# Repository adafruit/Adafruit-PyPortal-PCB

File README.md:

## Adafruit PyPortal - CircuitPython Powered Internet Display PCB

<br/>
<br/>
<br/>

PCB files for the Adafruit PyPortal - CircuitPython Powered Internet Display and PyPortal Pynt. Format is EagleCAD schematic and board layout
* https://www.adafruit.com/product/4116
* https://www.adafruit.com/product/4465
* https://www.adafruit.com/product/4444

### Description

**PyPortal**, our easy-to-use IoT device that allows you to create all the things for the “Internet of Things” in minutes. Make custom touch screen interface GUIs, all open-source, and Python-powered using tinyJSON / APIs to get news, stock, weather, cat photos, and more – all over Wi-Fi with the latest technologies. Create little pocket universes of joy that connect to something good. Rotate it 90 degrees, it’s a web-connected conference badge #badgelife.

The PyPortal uses an ATMEL (Microchip) ATSAMD51J20, and an Espressif ESP32 Wi-Fi coprocessor with TLS/SSL support built-in. PyPortal has a **3.2″ 320 x 240 color TFT** with resistive touch screen. PyPortal includes: speaker, light sensor, temperature sensor, NeoPixel, microSD card slot, 8MB flash, plug-in ports for I2C and 2 analog/digital pins, 3D files for custom enclosures / lanyard fastening. Open-source hardware, and Open-Source software, CircuitPython and Arduino. The device shows up as a USB drive and the code (Python) can be edited in any IDE, text editor, etc.

The PyPortal Pynt is the little sister to our popular PyPortal - zapped with a shink ray to take the design from a 3.2" diagonal down to 2.4" diagonal screen - but otherwise the same! **Compared to the PyPortal, the Pynt does not include a ADT7410 temperature sensor. Other than the ADT7410, the Pynt's display, processor, STEMMA conectors and WiFi have the exact same wiring as the original 3.2" PyPortal so all Arduino/CircuitPython code will run exactly the same - just smaller!**

The M4 and ESP32 are a great couple - and each bring their own strengths to this board. The SAMD51 M4 has native USB so it can show up like a disk drive, act as a MIDI or HID keyboard/mouse, and of course bootload and debug over a serial port. It also has DACs, ADC, PWM, and tons of GPIO. Meanwhile, the ESP32 has secure WiFi capabilities, and plenty of Flash and RAM to buffer sockets. By letting the ESP32 focus on the complex TLS/SSL computation and socket buffering, it frees up the SAMD51 to act as the user interface. You get a great programming experience thanks to the native USB with files available for drag-n-drop, and you don't have to spend a ton of processor time and memory to do SSL encryption/decryption and certificate management. It's the best of both worlds!

**Please note:** You may get a version with DigiKey + Analog Devices branding or in plain style. The hardware is identical.

### License

Adafruit invests time and resources providing this open source design, please support Adafruit and open-source hardware by purchasing products from [Adafruit](https://www.adafruit.com)!

Designed by Limor Fried/Ladyada for Adafruit Industries.

Creative Commons Attribution/Share-Alike, all text above must be included in any redistribution. See license.txt for additional details.

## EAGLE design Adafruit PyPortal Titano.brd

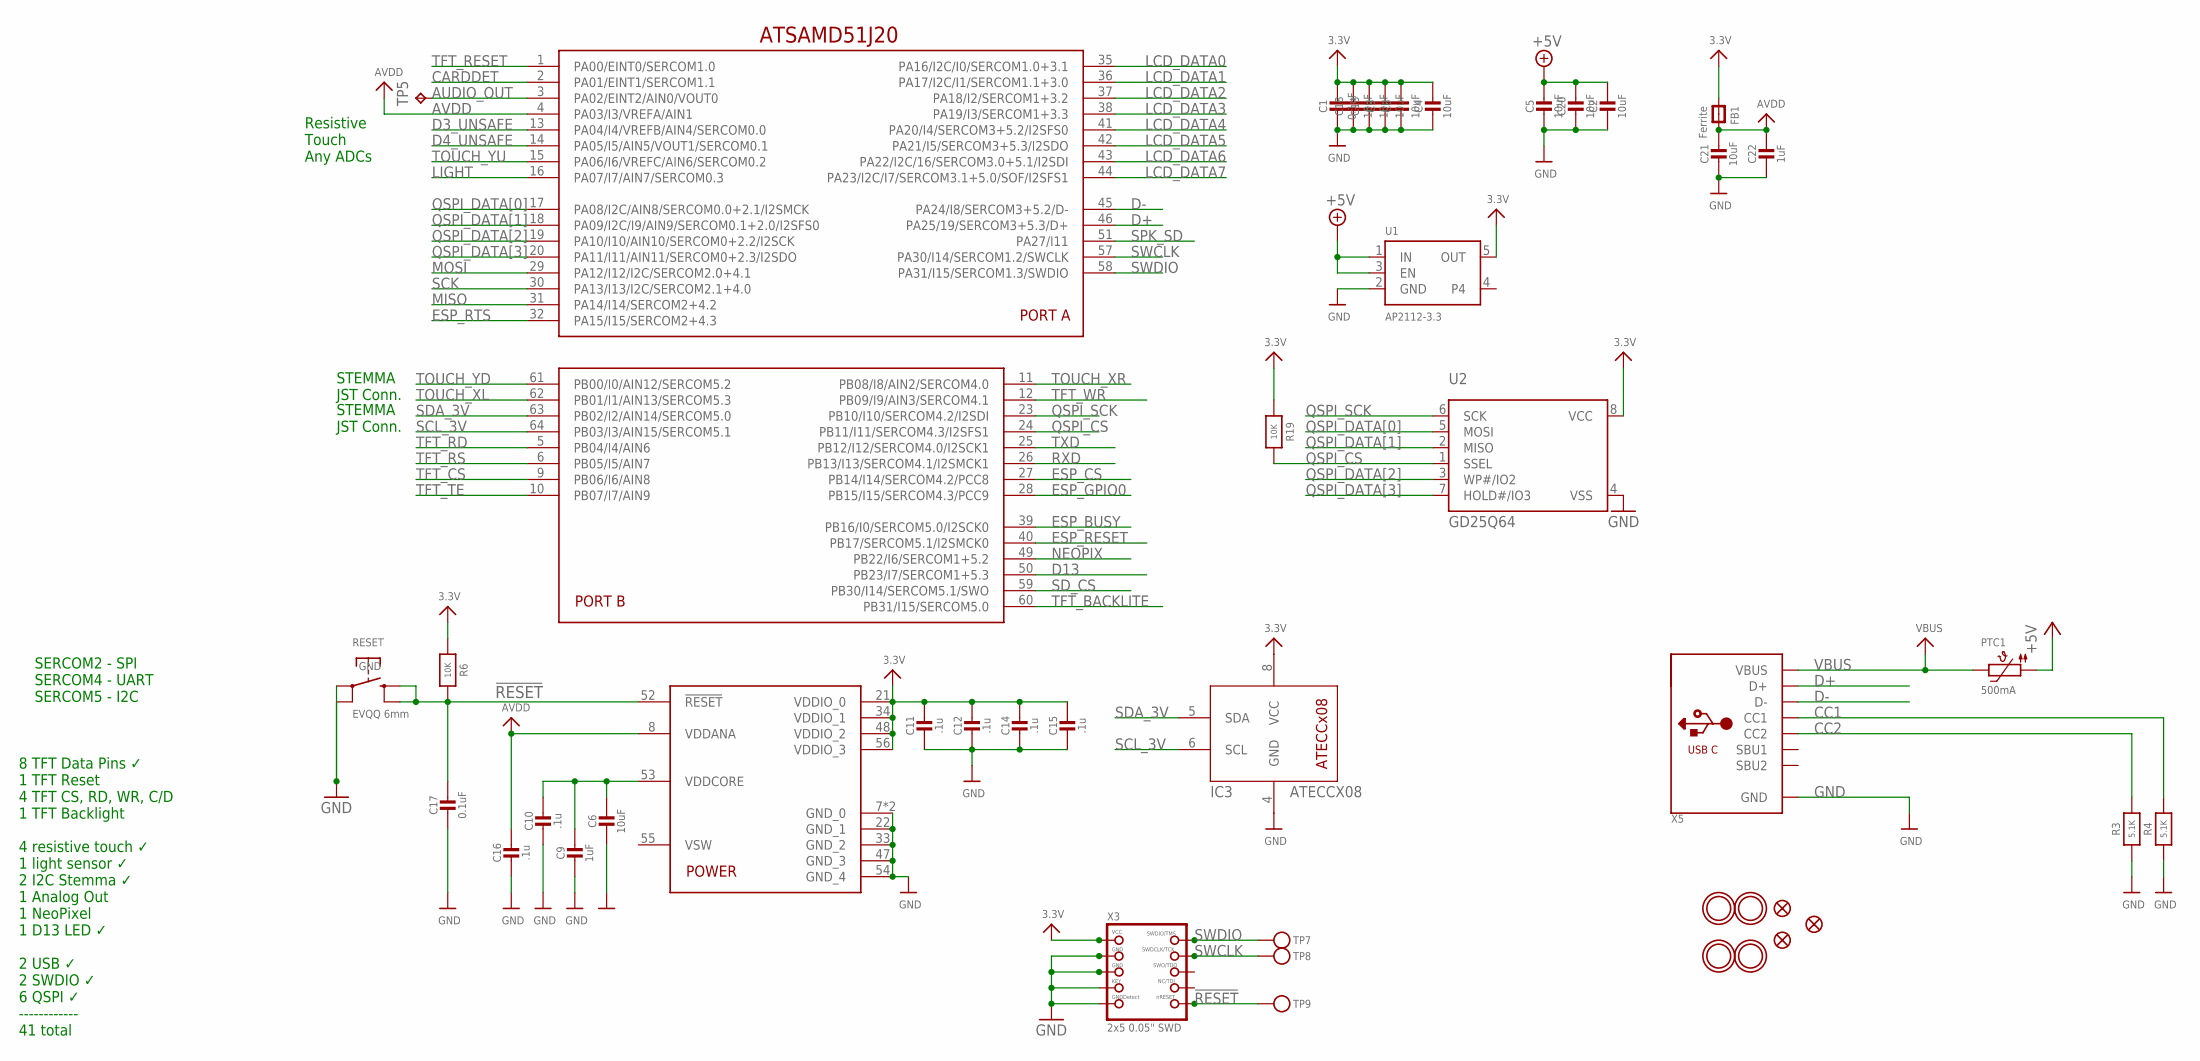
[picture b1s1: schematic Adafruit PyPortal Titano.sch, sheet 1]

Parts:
C1, C17: 0.1uF; 0603-NO
C2, C3, C4, C5, C6, C8, C13, C18, C20, C21: 10uF; 0805-NO
C9, C22: 1uF; 0603-NO
C10, C11, C12, C14, C15, C16: .1u; 0603-NO
FB1: Ferrite; 0805-NO
IC3: ATECCX08; SOIC8_150MIL
PTC1: 500mA; 1206
R3, R4: 5.1K; 0603-NO
R6, R19: 10K; 0603-NO
RESET: EVQQ 6mm; EVQ-Q2_SMALLER
TP5: TPTP15R; TP15R
TP7, TP8, TP9: TESTPOINTROUND1.5MM; TESTPOINT_ROUND_1.5MM
U1: AP2112-3.3; SOT23-5
U2: GD25Q64; SOIC8_208MIL
U$2: ATSAMD51J20; PQFN64-1
U$7, U$15, U$16, U$17: MOUNTINGHOLE3.0THIN; MOUNTINGHOLE_3.0_PLATEDTHIN
U$9, U$11, U$23: FIDUCIAL_1MM
X3: 2x5 0.05" SWD; 2X05_1.27MM_BOX_POSTS
X5: USB_C; USB_C_CUSB31-CFM2AX-01-X

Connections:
3.3V: C1.1, C3.1, C4.1, C8.1, C11.2, C12.2, C13.1, C14.2, C15.2, C18.1, FB1.1, IC3.8 (VCC), R6.1, R19.1, U1.5 (OUT), U2.8 (VCC), U$2.21 (VDDIO_0), U$2.34 (VDDIO_1), U$2.48 (VDDIO_2), U$2.56 (VDDIO_3), X3.1 (VCC); also elsewhere on the board
!RESET: C17.2, R6.2, RESET.B (S), RESET.B' (S1), TP9.P$1, U$2.52 (!RESET), X3.10 (NRESET)
+5V: C2.1, C5.1, C20.1, PTC1.1, U1.1 (IN), U1.3 (EN); also elsewhere on the board
AUDIO_OUT: TP5.TP, U$2.3 (PA02/EINT2/AIN0/VOUT0); also elsewhere on the board
AVDD: C16.2, C21.1, C22.1, FB1.2, U$2.4 (PA03/I3/VREFA/AIN1), U$2.8 (VDDANA)
CARDDET: U$2.2 (PA01/EINT1/SERCOM1.1); also elsewhere on the board
CC1: R4.2, X5.A5 (CC1)
CC2: R3.2, X5.B5 (CC2)
D3_UNSAFE: U$2.13 (PA04/I4/VREFB/AIN4/SERCOM0.0); also elsewhere on the board
D4_UNSAFE: U$2.14 (PA05/I5/AIN5/VOUT1/SERCOM0.1); also elsewhere on the board
D13: U$2.50 (PB23/I7/SERCOM1+5.3); also elsewhere on the board
D+: U$2.46 (PA25/19/SERCOM3+5.3/D+), X5.A6 (D+), X5.B6 (D+)
D-: U$2.45 (PA24/I8/SERCOM3+5.2/D-), X5.A7 (D-), X5.B7 (D-)
ESP_BUSY: U$2.39 (PB16/I0/SERCOM5.0/I2SCK0); also elsewhere on the board
ESP_CS: U$2.27 (PB14/I14/SERCOM4.2/PCC8); also elsewhere on the board
ESP_GPIO0: U$2.28 (PB15/I15/SERCOM4.3/PCC9); also elsewhere on the board
ESP_RESET: U$2.40 (PB17/SERCOM5.1/I2SMCK0); also elsewhere on the board
ESP_RTS: U$2.32 (PA15/I15/SERCOM2+4.3); also elsewhere on the board
GND: C1.2, C2.2, C3.2, C4.2, C5.2, C6.2, C8.2, C9.2, C10.1, C11.1, C12.1, C13.2, C14.1, C15.1, C16.1, C17.1, C18.2, C20.2, C21.2, C22.2, IC3.4 (GND), R3.1, R4.1, RESET.A, RESET.A' (P1), U1.2 (GND), U2.4 (VSS), U$2.7 (GND_0), U$2.22 (GND_1), U$2.33 (GND_2), U$2.47 (GND_3), U$2.54 (GND_4), U$2.EXP (GND_0), X3.3 (GND), X3.5 (GND), X3.7 (KEY), X3.9 (GNDDETECT), X5.A1B12 (GND), X5.B1A12 (GND); also elsewhere on the board
LCD_DATA0: U$2.35 (PA16/I2C/I0/SERCOM1.0+3.1); also elsewhere on the board
LCD_DATA1: U$2.36 (PA17/I2C/I1/SERCOM1.1+3.0); also elsewhere on the board
LCD_DATA2: U$2.37 (PA18/I2/SERCOM1+3.2); also elsewhere on the board
LCD_DATA3: U$2.38 (PA19/I3/SERCOM1+3.3); also elsewhere on the board
LCD_DATA4: U$2.41 (PA20/I4/SERCOM3+5.2/I2SFS0); also elsewhere on the board
LCD_DATA5: U$2.42 (PA21/I5/SERCOM3+5.3/I2SDO); also elsewhere on the board
LCD_DATA6: U$2.43 (PA22/I2C/16/SERCOM3.0+5.1/I2SDI); also elsewhere on the board
LCD_DATA7: U$2.44 (PA23/I2C/I7/SERCOM3.1+5.0/SOF/I2SFS1); also elsewhere on the board
LIGHT: U$2.16 (PA07/I7/AIN7/SERCOM0.3); also elsewhere on the board
MISO: U$2.31 (PA14/I14/SERCOM2+4.2); also elsewhere on the board
MOSI: U$2.29 (PA12/I12/I2C/SERCOM2.0+4.1); also elsewhere on the board
NEOPIX: U$2.49 (PB22/I6/SERCOM1+5.2); also elsewhere on the board
QSPI_CS: R19.2, U2.1 (SSEL), U$2.24 (PB11/I11/SERCOM4.3/I2SFS1)
QSPI_DATA[0]: U2.5 (MOSI), U$2.17 (PA08/I2C/AIN8/SERCOM0.0+2.1/I2SMCK)
QSPI_DATA[1]: U2.2 (MISO), U$2.18 (PA09/I2C/I9/AIN9/SERCOM0.1+2.0/I2SFS0)
QSPI_DATA[2]: U2.3 (WP#/IO2), U$2.19 (PA10/I10/AIN10/SERCOM0+2.2/I2SCK)
QSPI_DATA[3]: U2.7 (HOLD#/IO3), U$2.20 (PA11/I11/AIN11/SERCOM0+2.3/I2SDO)
QSPI_SCK: U2.6 (SCK), U$2.23 (PB10/I10/SERCOM4.2/I2SDI)
RXD: U$2.26 (PB13/I13/SERCOM4.1/I2SMCK1); also elsewhere on the board
SCK: U$2.30 (PA13/I13/I2C/SERCOM2.1+4.0); also elsewhere on the board
SCL_3V: IC3.6 (SCL), U$2.64 (PB03/I3/AIN15/SERCOM5.1); also elsewhere on the board
SDA_3V: IC3.5 (SDA), U$2.63 (PB02/I2/AIN14/SERCOM5.0); also elsewhere on the board
SD_CS: U$2.59 (PB30/I14/SERCOM5.1/SWO); also elsewhere on the board
SPK_SD: U$2.51 (PA27/I11); also elsewhere on the board
SWCLK: TP8.P$1, U$2.57 (PA30/I14/SERCOM1.2/SWCLK), X3.4 (SWDCLK)
SWDIO: TP7.P$1, U$2.58 (PA31/I15/SERCOM1.3/SWDIO), X3.2 (SWDIO)
TFT_BACKLITE: U$2.60 (PB31/I15/SERCOM5.0); also elsewhere on the board
TFT_CS: U$2.9 (PB06/I6/AIN8); also elsewhere on the board
TFT_RD: U$2.5 (PB04/I4/AIN6); also elsewhere on the board
TFT_RESET: U$2.1 (PA00/EINT0/SERCOM1.0); also elsewhere on the board
TFT_RS: U$2.6 (PB05/I5/AIN7); also elsewhere on the board
TFT_TE: U$2.10 (PB07/I7/AIN9); also elsewhere on the board
TFT_WR: U$2.12 (PB09/I9/AIN3/SERCOM4.1); also elsewhere on the board
TOUCH_XL: U$2.62 (PB01/I1/AIN13/SERCOM5.3); also elsewhere on the board
TOUCH_XR: U$2.11 (PB08/I8/AIN2/SERCOM4.0); also elsewhere on the board
TOUCH_YD: U$2.61 (PB00/I0/AIN12/SERCOM5.2); also elsewhere on the board
TOUCH_YU: U$2.15 (PA06/I6/VREFC/AIN6/SERCOM0.2); also elsewhere on the board
TXD: U$2.25 (PB12/I12/SERCOM4.0/I2SCK1); also elsewhere on the board
VBUS: PTC1.2, X5.A4B9 (VBUS), X5.B4A9 (VBUS)
VDDCORE: C6.1, C9.1, C10.2, U$2.53 (VDDCORE)

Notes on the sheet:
ATSAMD51J20
8 TFT Data Pins ✓ 1 TFT Reset 4 TFT CS, RD, WR, C/D 1 TFT Backlight 4 resistive touch ✓ 1 light sensor ✓ 2 I2C Stemma ✓ 1 Analog Out 1 NeoPixel 1 D13 LED ✓ 2 USB ✓ 2 SWDIO ✓ 6 QSPI ✓ ------------ 41 total
STEMMA JST Conn.
Resistive Touch Any ADCs
SERCOM2 - SPI SERCOM4 - UART SERCOM5 - I2C

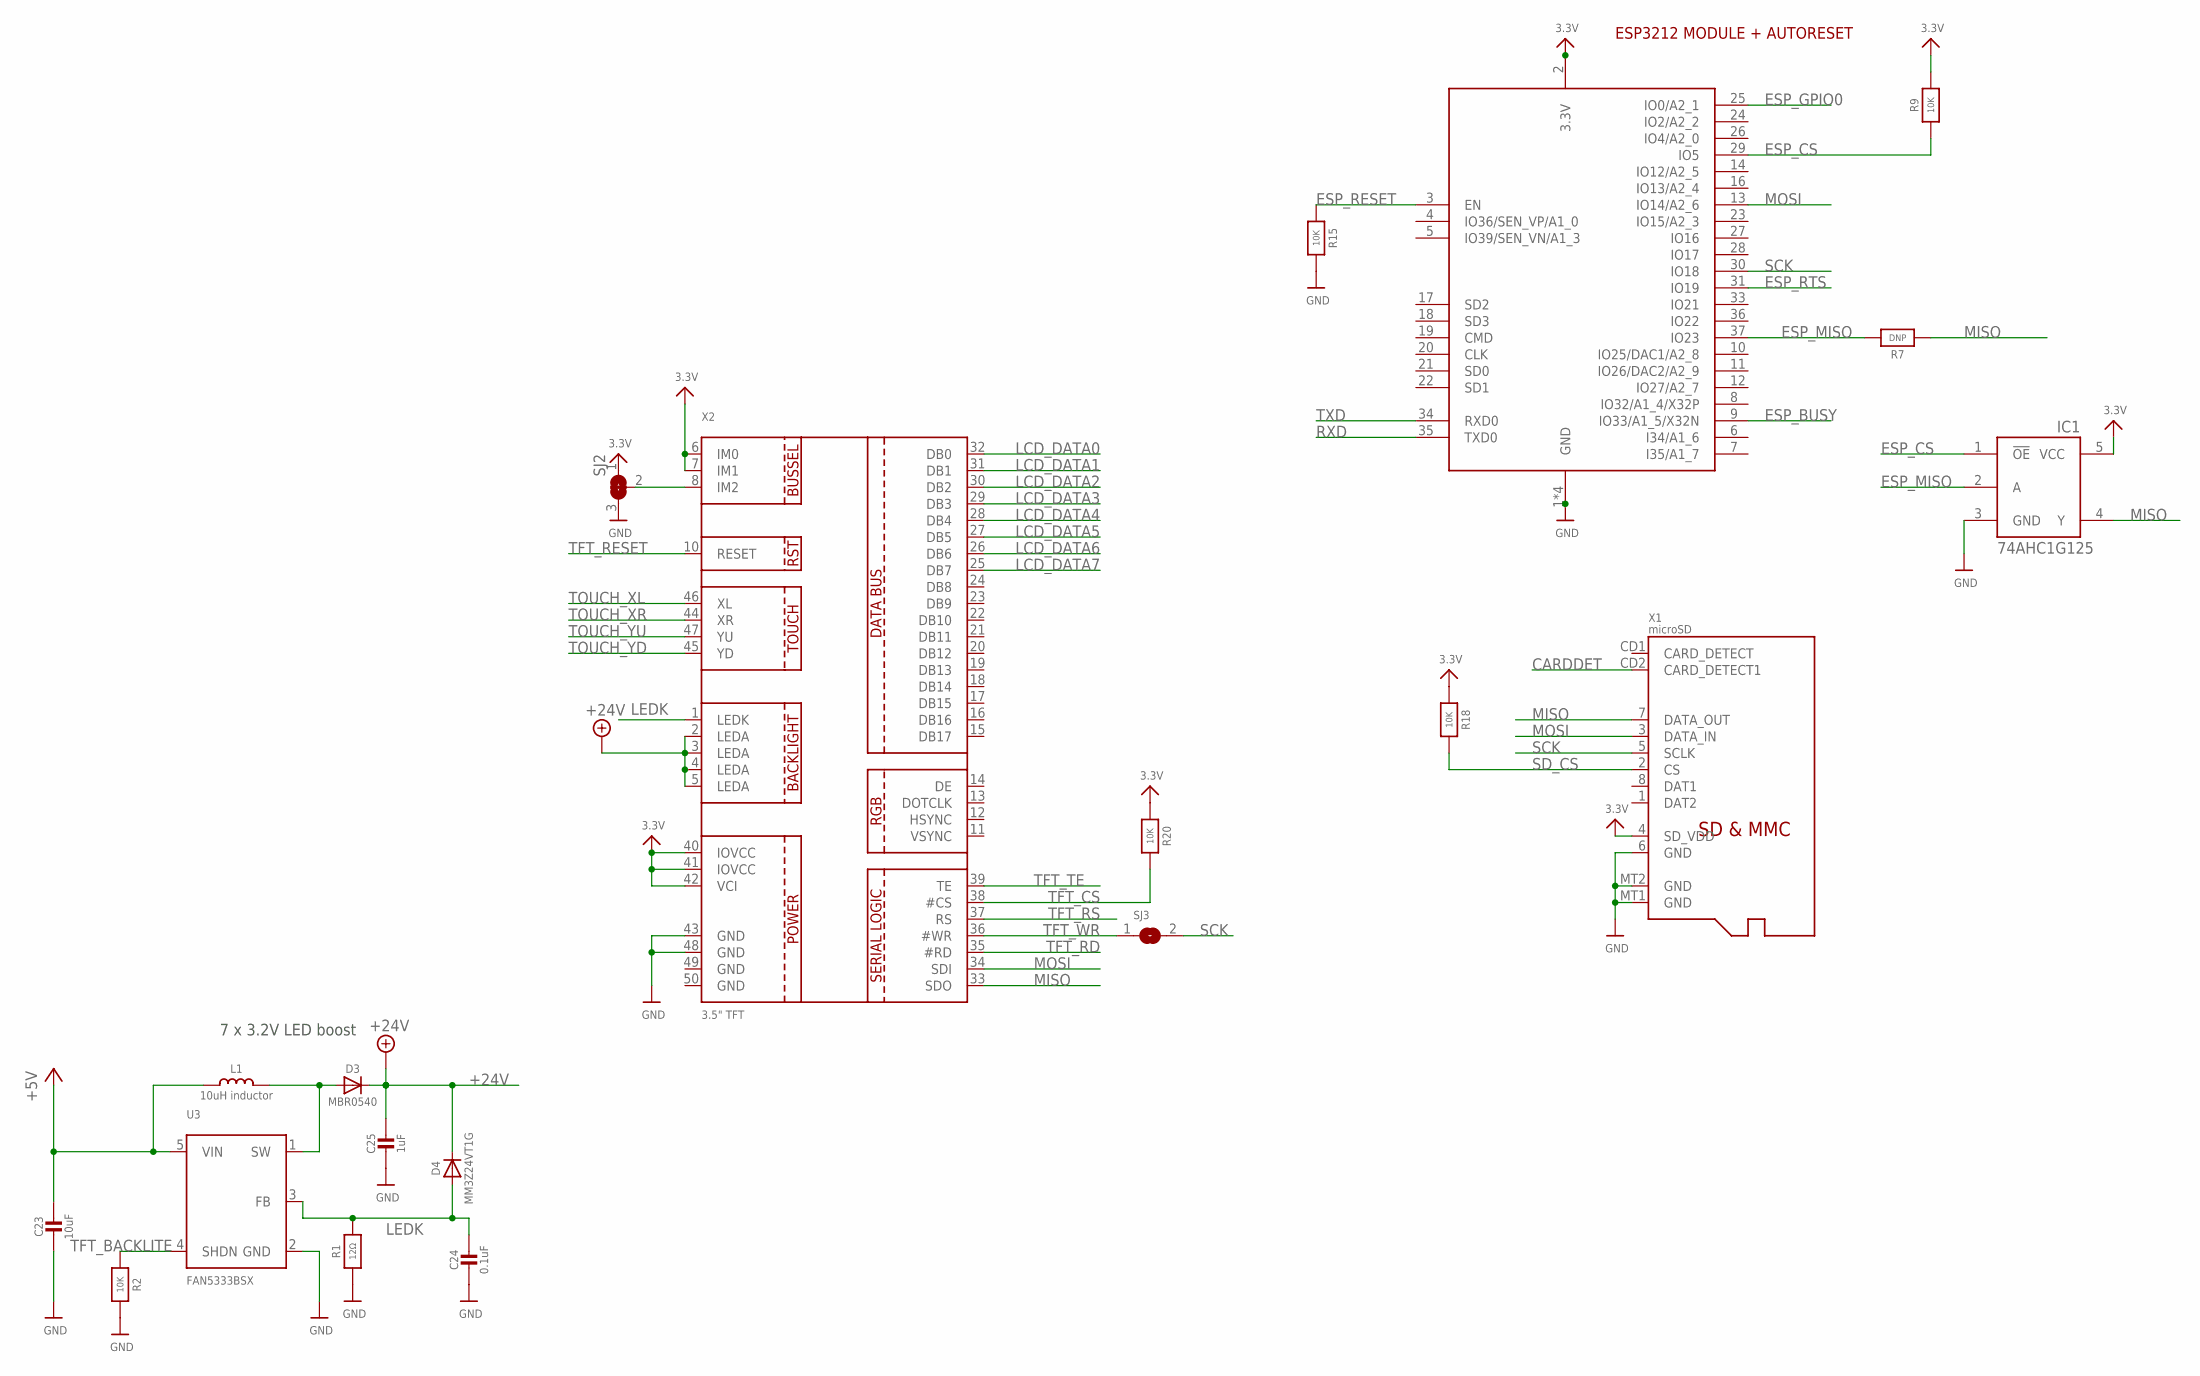
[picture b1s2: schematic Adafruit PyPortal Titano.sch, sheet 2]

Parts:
C23: 10uF; 0805-NO
C24: 0.1uF; 0805-NO
C25: 1uF; 0805-NO
D3: MBR0540; SOD-123
D4: MM3Z24VT1G; SMADIODE
IC1: 74AHC1G125; SOT23-5L
L1: 10uH inductor; INDUCTOR_5X5MM_NR5040_NOTHERMALS
R1: 12Ω; 0805-NO
R2, R9, R15, R18, R20: 10K; 0603-NO
R7: DNP; 0603-NO
SJ2: SOLDERJUMPER_2WAY; SOLDERJUMPER_2WAY_OPEN_NOPASTE
SJ3: SOLDERJUMPER; SOLDERJUMPER_ARROW_NOPASTE
U3: FAN5333BSX; SOT23-5
X1: microSD; MICROSD
X2: 3.5" TFT; TFT_3.5IN_320X480_50PIN
X6: ESP32_WROOM32; WROOM32

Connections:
3.3V: IC1.5 (VCC), R9.2, R18.1, R20.1, SJ2.1, X1.4 (SD_VDD), X2.6 (IM0), X2.7 (IM1), X2.40 (IOVCC), X2.41 (IOVCC), X2.42 (VCI), X6.2 (3.3V); also elsewhere on the board
+5V: C23.1, L1.P$1 (1), U3.5 (VIN); also elsewhere on the board
+24V: C25.1, D3.C, D4.C, X2.2 (LEDA), X2.3 (LEDA), X2.4 (LEDA), X2.5 (LEDA)
CARDDET: X1.CD2 (CARD_DETECT1); also elsewhere on the board
ESP_BUSY: X6.9 (IO33/A1_5/X32N); also elsewhere on the board
ESP_CS: IC1.1 (!OE), R9.1, X6.29 (IO5); also elsewhere on the board
ESP_GPIO0: X6.25 (IO0/A2_1); also elsewhere on the board
ESP_MISO: IC1.2 (A), R7.2, X6.37 (IO23)
ESP_RESET: R15.1, X6.3 (EN); also elsewhere on the board
ESP_RTS: X6.31 (IO19); also elsewhere on the board
GND: C23.2, C24.2, C25.2, IC1.3 (GND), R1.1, R2.2, R15.2, SJ2.3, U3.2 (GND), X1.6 (GND), X1.MT1 (GND), X1.MT2 (GND), X2.43 (GND), X2.48 (GND), X6.1 (GND), X6.15 (GND), X6.38 (GND), X6.P$1 (GND); also elsewhere on the board
LCD_DATA0: X2.32 (DB0); also elsewhere on the board
LCD_DATA1: X2.31 (DB1); also elsewhere on the board
LCD_DATA2: X2.30 (DB2); also elsewhere on the board
LCD_DATA3: X2.29 (DB3); also elsewhere on the board
LCD_DATA4: X2.28 (DB4); also elsewhere on the board
LCD_DATA5: X2.27 (DB5); also elsewhere on the board
LCD_DATA6: X2.26 (DB6); also elsewhere on the board
LCD_DATA7: X2.25 (DB7); also elsewhere on the board
LEDK: C24.1, D4.A, R1.2, U3.3 (FB), X2.1 (LEDK)
MISO: IC1.4 (Y), R7.1, X1.7 (DATA_OUT), X2.33 (SDO); also elsewhere on the board
MOSI: X1.3 (DATA_IN), X2.34 (SDI), X6.13 (IO14/A2_6); also elsewhere on the board
unnamed: SJ2.2, X2.8 (IM2)
unnamed: D3.A, L1.P$2 (2), U3.1 (SW)
RXD: X6.35 (TXD0); also elsewhere on the board
SCK: SJ3.2, X1.5 (SCLK), X6.30 (IO18); also elsewhere on the board
SD_CS: R18.2, X1.2 (CS); also elsewhere on the board
TFT_BACKLITE: R2.1, U3.4 (SHDN); also elsewhere on the board
TFT_CS: R20.2, X2.38 (#CS); also elsewhere on the board
TFT_RD: X2.35 (#RD); also elsewhere on the board
TFT_RESET: X2.10 (RESET); also elsewhere on the board
TFT_RS: X2.37 (RS); also elsewhere on the board
TFT_TE: X2.39 (TE); also elsewhere on the board
TFT_WR: SJ3.1, X2.36 (#WR); also elsewhere on the board
TOUCH_XL: X2.46 (XL); also elsewhere on the board
TOUCH_XR: X2.44 (XR); also elsewhere on the board
TOUCH_YD: X2.45 (YD); also elsewhere on the board
TOUCH_YU: X2.47 (YU); also elsewhere on the board
TXD: X6.34 (RXD0); also elsewhere on the board

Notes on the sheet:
ESP3212 MODULE + AUTORESET
7 x 3.2V LED boost

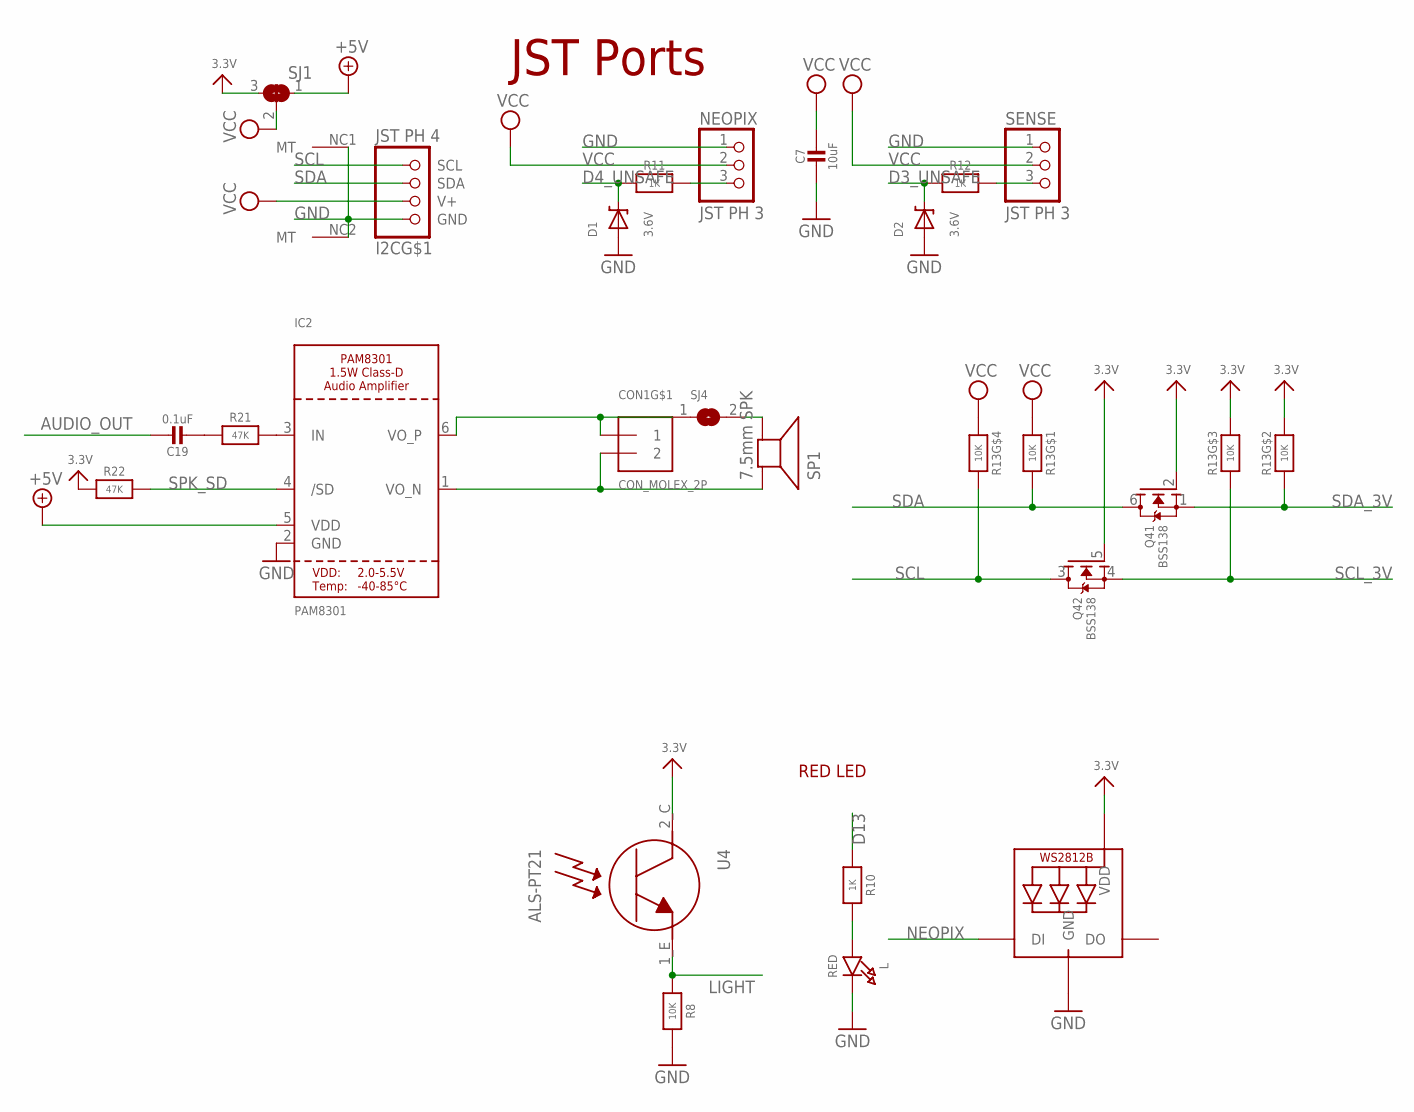
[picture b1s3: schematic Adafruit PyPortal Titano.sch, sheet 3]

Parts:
C7: 10uF; 0805-NO
C19: 0.1uF; 0603-NO
CON1: CON_MOLEX_2P; 53398-0271
D1, D2: 3.6V; SOD-323
I2C: JST PH 4; JSTPH4
IC2: PAM8301; SOT23-6
L: RED; CHIPLED_0805_NOOUTLINE
LED1: WS2812B3535; LED3535
NEOPIX: JST PH 3; JSTPH3
Q4: BSS138; SOT363
R8: 10K; 0603-NO
R10, R11, R12: 1K; 0603-NO
R13: 10K; RESPACK_4X0603
R21, R22: 47K; 0603-NO
SENSE: JST PH 3; JSTPH3
SJ1: SOLDERJUMPER_2WAY; SOLDERJUMPER_2WAY_OPEN_NOPASTE
SJ4: SOLDERJUMPERCLOSED; SOLDERJUMPER_CLOSEDWIRE
SP1: 7.5mm SPK; BUZZER_SMT_7.5MM
U4: ALS-PT21; ALS-PT26-21C

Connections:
3.3V: LED1.2 (VDD), Q4.2 (G), Q4.5 (G), R13.2 (1), R13.3 (1), R22.1, SJ1.3, U4.2_C (C); also elsewhere on the board
+5V: IC2.5 (VDD), SJ1.1; also elsewhere on the board
AUDIO_OUT: C19.1; also elsewhere on the board
D3: R12.1, SENSE.3
D3_UNSAFE: D2.C, R12.2; also elsewhere on the board
D4: NEOPIX.3, R11.1
D4_UNSAFE: D1.C, R11.2; also elsewhere on the board
D13: R10.1; also elsewhere on the board
GND: C7.2, D1.A, D2.A, I2C.1 (GND), I2C.NC1 (MT), I2C.NC2 (MT), IC2.2 (GND), L.C, LED1.4 (GND), NEOPIX.1, R8.1, SENSE.1; also elsewhere on the board
LIGHT: R8.2, U4.1_E (E); also elsewhere on the board
unnamed: L.A, R10.2
unnamed: C19.2, R21.1
unnamed: IC2.3 (IN), R21.2
unnamed: SJ4.2, SP1.-
NEOPIX: LED1.1 (DI); also elsewhere on the board
SCL: I2C.4 (SCL), Q4.3 (D), R13.5 (2)
SCL_3V: Q4.4 (S), R13.6 (2); also elsewhere on the board
SDA: I2C.3 (SDA), Q4.6 (D), R13.8 (2)
SDA_3V: Q4.1 (S), R13.7 (2); also elsewhere on the board
SPKR+: CON1.2, IC2.1 (VO_N), SP1.+
SPK_SD: IC2.4 (/SD), R22.2; also elsewhere on the board
SPRK-: CON1.1, IC2.6 (VO_P), SJ4.1
VCC: C7.1, I2C.2 (V+), NEOPIX.2, R13.1, R13.4 (1), SENSE.2, SJ1.2

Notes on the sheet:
RED LED
JST Ports

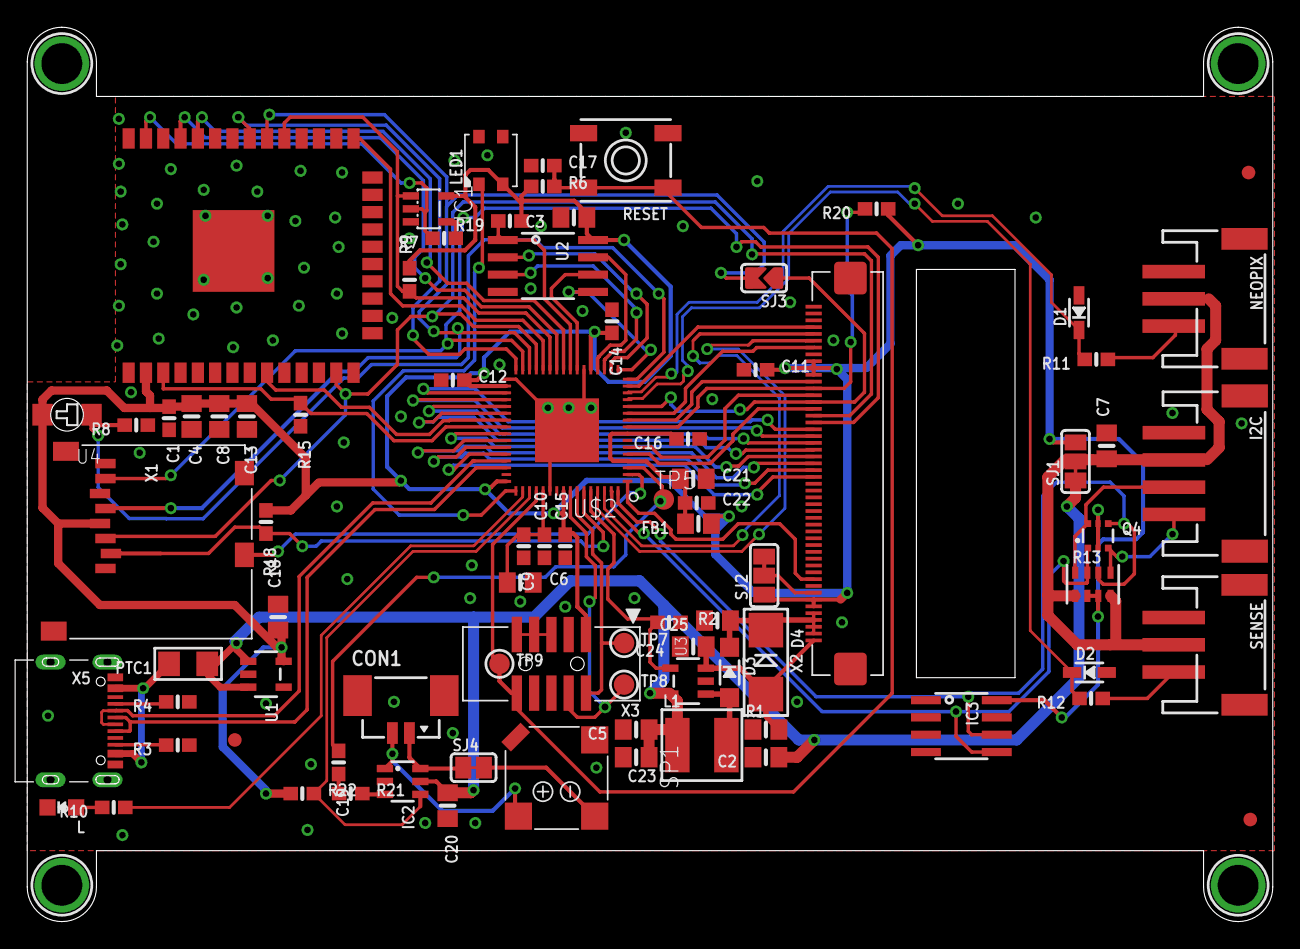
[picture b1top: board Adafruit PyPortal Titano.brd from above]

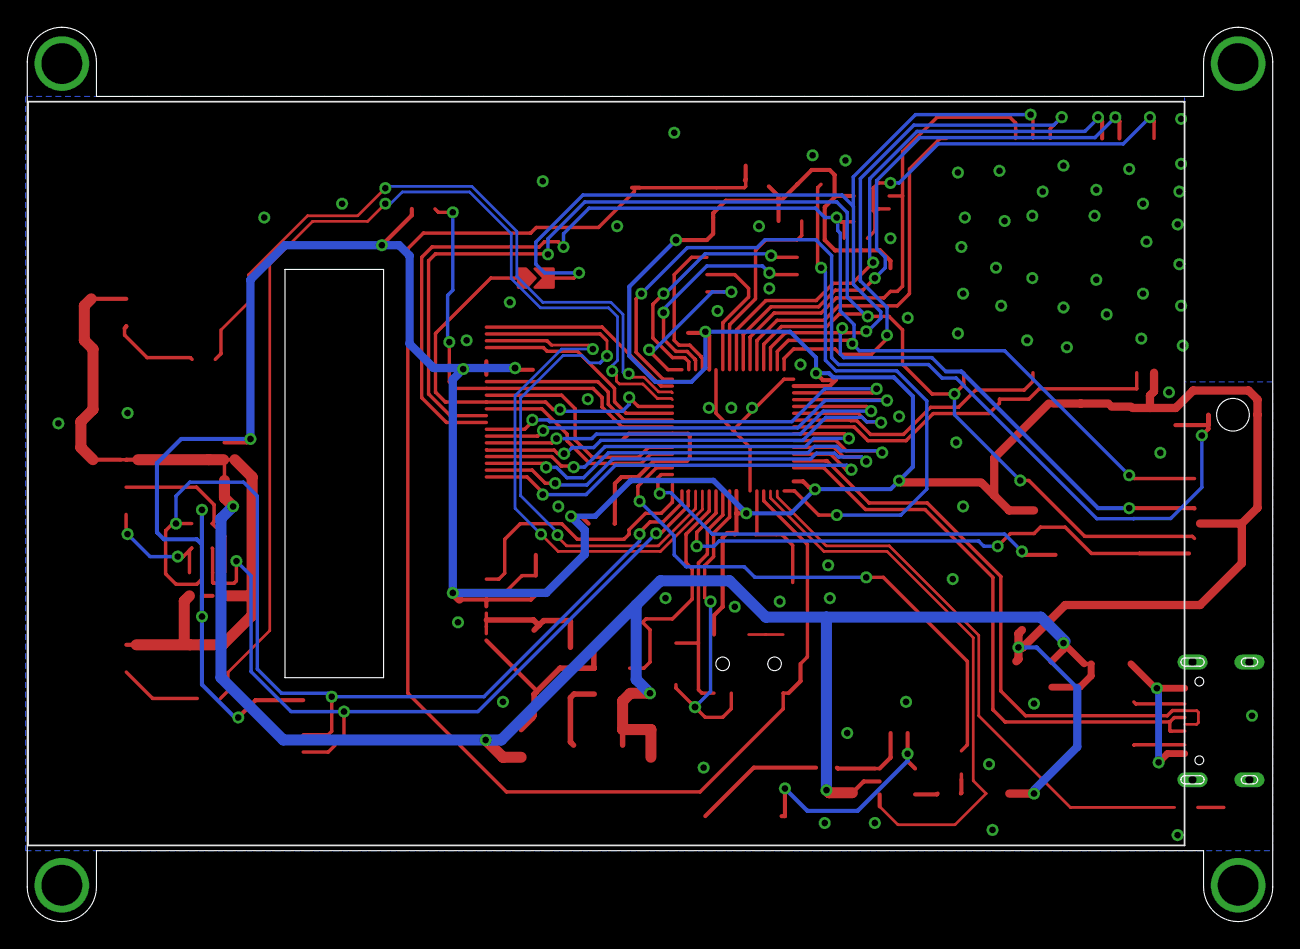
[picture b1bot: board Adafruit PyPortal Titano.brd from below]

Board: 2 copper layers, 91.4 x 65.7 mm, 89 parts (2 on the bottom side), 75 nets.

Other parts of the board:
U$19: PYPORTALTITANO_BOT
U$54: PYPORTALTITANO_TOP

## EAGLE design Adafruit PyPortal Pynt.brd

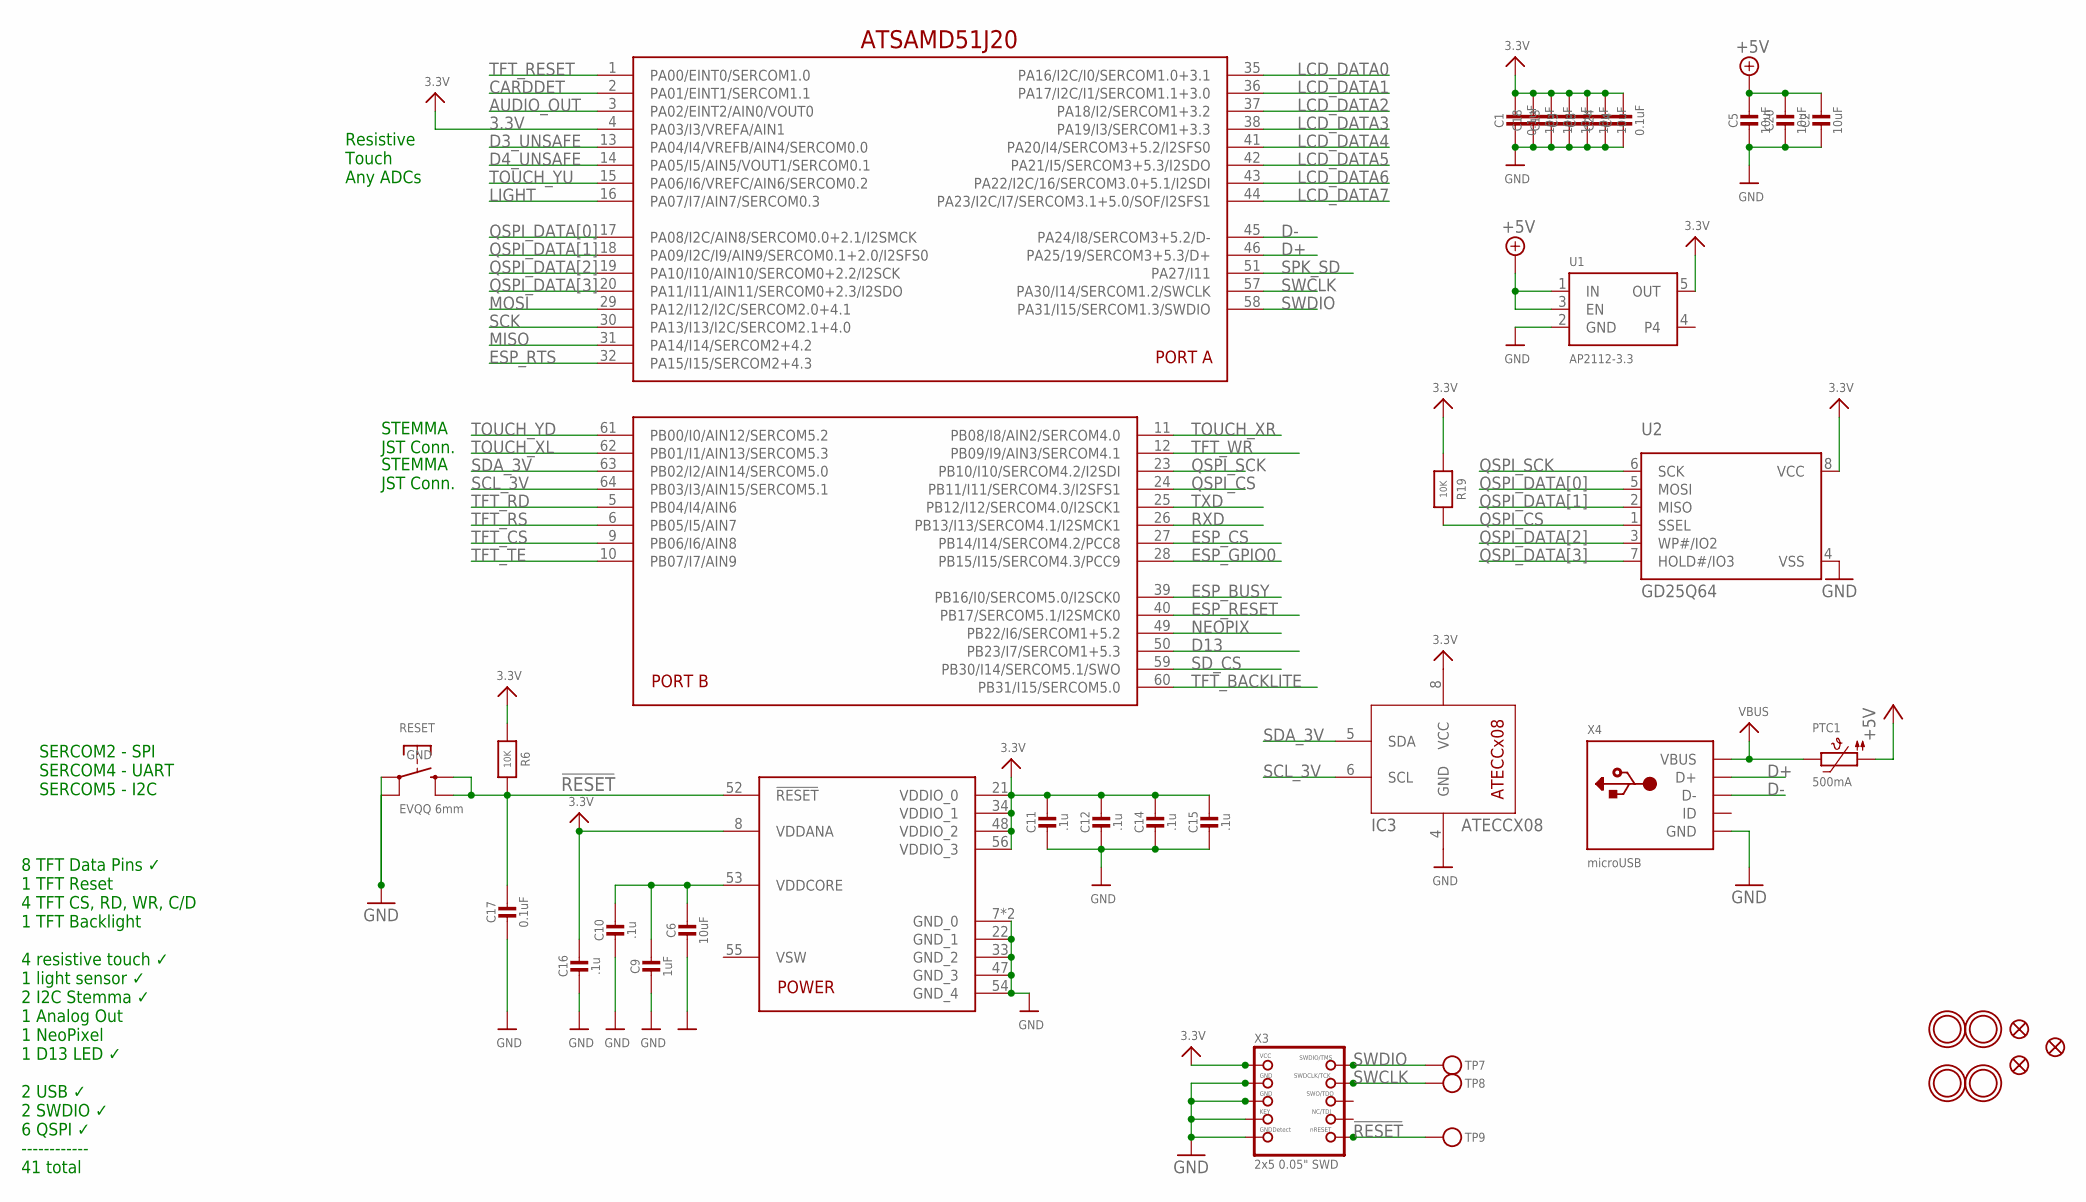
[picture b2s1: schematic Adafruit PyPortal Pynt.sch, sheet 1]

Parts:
C1, C17: 0.1uF; 0603-NO
C2, C3, C5, C6, C8, C13, C18, C20, C24: 10uF; 0805-NO
C4: 0.1uF; 0805-NO
C9: 1uF; 0603-NO
C10, C11, C12, C14, C15, C16: .1u; 0603-NO
IC3: ATECCX08; SOIC8_150MIL
PTC1: 500mA; 1206
R6, R19: 10K; 0603-NO
RESET: EVQQ 6mm; EVQ-Q2_SMALLER
TP7, TP8, TP9: TESTPOINTROUND1.5MM; TESTPOINT_ROUND_1.5MM
U1: AP2112-3.3; SOT23-5
U2: GD25Q64; SOIC8_208MIL
U$2: ATSAMD51J20; PQFN64-1
U$7, U$15, U$16, U$17: MOUNTINGHOLE3.0THIN; MOUNTINGHOLE_3.0_PLATEDTHIN
U$9, U$11, U$23: FIDUCIAL_1MM
X3: 2x5 0.05" SWD; 2X05_1.27MM_SMT
X4: microUSB; 4UCONN_20329_NARROW

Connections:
3.3V: C1.1, C3.1, C4.1, C8.1, C11.2, C12.2, C13.1, C14.2, C15.2, C16.2, C18.1, C24.1, IC3.8 (VCC), R6.1, R19.1, U1.5 (OUT), U2.8 (VCC), U$2.4 (PA03/I3/VREFA/AIN1), U$2.8 (VDDANA), U$2.21 (VDDIO_0), U$2.34 (VDDIO_1), U$2.48 (VDDIO_2), U$2.56 (VDDIO_3), X3.1 (VCC); also elsewhere on the board
!RESET: C17.2, R6.2, RESET.B (S), RESET.B' (S1), TP9.P$1, U$2.52 (!RESET), X3.10 (NRESET)
+5V: C2.1, C5.1, C20.1, PTC1.1, U1.1 (IN), U1.3 (EN); also elsewhere on the board
AUDIO_OUT: U$2.3 (PA02/EINT2/AIN0/VOUT0); also elsewhere on the board
CARDDET: U$2.2 (PA01/EINT1/SERCOM1.1); also elsewhere on the board
D3_UNSAFE: U$2.13 (PA04/I4/VREFB/AIN4/SERCOM0.0); also elsewhere on the board
D4_UNSAFE: U$2.14 (PA05/I5/AIN5/VOUT1/SERCOM0.1); also elsewhere on the board
D13: U$2.50 (PB23/I7/SERCOM1+5.3); also elsewhere on the board
D+: U$2.46 (PA25/19/SERCOM3+5.3/D+), X4.D+
D-: U$2.45 (PA24/I8/SERCOM3+5.2/D-), X4.D-
ESP_BUSY: U$2.39 (PB16/I0/SERCOM5.0/I2SCK0); also elsewhere on the board
ESP_CS: U$2.27 (PB14/I14/SERCOM4.2/PCC8); also elsewhere on the board
ESP_GPIO0: U$2.28 (PB15/I15/SERCOM4.3/PCC9); also elsewhere on the board
ESP_RESET: U$2.40 (PB17/SERCOM5.1/I2SMCK0); also elsewhere on the board
ESP_RTS: U$2.32 (PA15/I15/SERCOM2+4.3); also elsewhere on the board
GND: C1.2, C2.2, C3.2, C4.2, C5.2, C6.2, C8.2, C9.2, C10.1, C11.1, C12.1, C13.2, C14.1, C15.1, C16.1, C17.1, C18.2, C20.2, C24.2, IC3.4 (GND), RESET.A, RESET.A' (P1), U1.2 (GND), U2.4 (VSS), U$2.7 (GND_0), U$2.22 (GND_1), U$2.33 (GND_2), U$2.47 (GND_3), U$2.54 (GND_4), U$2.EXP (GND_0), X3.3 (GND), X3.5 (GND), X3.7 (KEY), X3.9 (GNDDETECT), X4.BASE@1 (GND), X4.BASE@2 (GND), X4.GND, X4.SPRT@1 (GND), X4.SPRT@2 (GND), X4.SPRT@3 (GND), X4.SPRT@4 (GND); also elsewhere on the board
LCD_DATA0: U$2.35 (PA16/I2C/I0/SERCOM1.0+3.1); also elsewhere on the board
LCD_DATA1: U$2.36 (PA17/I2C/I1/SERCOM1.1+3.0); also elsewhere on the board
LCD_DATA2: U$2.37 (PA18/I2/SERCOM1+3.2); also elsewhere on the board
LCD_DATA3: U$2.38 (PA19/I3/SERCOM1+3.3); also elsewhere on the board
LCD_DATA4: U$2.41 (PA20/I4/SERCOM3+5.2/I2SFS0); also elsewhere on the board
LCD_DATA5: U$2.42 (PA21/I5/SERCOM3+5.3/I2SDO); also elsewhere on the board
LCD_DATA6: U$2.43 (PA22/I2C/16/SERCOM3.0+5.1/I2SDI); also elsewhere on the board
LCD_DATA7: U$2.44 (PA23/I2C/I7/SERCOM3.1+5.0/SOF/I2SFS1); also elsewhere on the board
LIGHT: U$2.16 (PA07/I7/AIN7/SERCOM0.3); also elsewhere on the board
MISO: U$2.31 (PA14/I14/SERCOM2+4.2); also elsewhere on the board
MOSI: U$2.29 (PA12/I12/I2C/SERCOM2.0+4.1); also elsewhere on the board
NEOPIX: U$2.49 (PB22/I6/SERCOM1+5.2); also elsewhere on the board
QSPI_CS: R19.2, U2.1 (SSEL), U$2.24 (PB11/I11/SERCOM4.3/I2SFS1)
QSPI_DATA[0]: U2.5 (MOSI), U$2.17 (PA08/I2C/AIN8/SERCOM0.0+2.1/I2SMCK)
QSPI_DATA[1]: U2.2 (MISO), U$2.18 (PA09/I2C/I9/AIN9/SERCOM0.1+2.0/I2SFS0)
QSPI_DATA[2]: U2.3 (WP#/IO2), U$2.19 (PA10/I10/AIN10/SERCOM0+2.2/I2SCK)
QSPI_DATA[3]: U2.7 (HOLD#/IO3), U$2.20 (PA11/I11/AIN11/SERCOM0+2.3/I2SDO)
QSPI_SCK: U2.6 (SCK), U$2.23 (PB10/I10/SERCOM4.2/I2SDI)
RXD: U$2.26 (PB13/I13/SERCOM4.1/I2SMCK1); also elsewhere on the board
SCK: U$2.30 (PA13/I13/I2C/SERCOM2.1+4.0); also elsewhere on the board
SCL_3V: IC3.6 (SCL), U$2.64 (PB03/I3/AIN15/SERCOM5.1); also elsewhere on the board
SDA_3V: IC3.5 (SDA), U$2.63 (PB02/I2/AIN14/SERCOM5.0); also elsewhere on the board
SD_CS: U$2.59 (PB30/I14/SERCOM5.1/SWO); also elsewhere on the board
SPK_SD: U$2.51 (PA27/I11); also elsewhere on the board
SWCLK: TP8.P$1, U$2.57 (PA30/I14/SERCOM1.2/SWCLK), X3.4 (SWDCLK)
SWDIO: TP7.P$1, U$2.58 (PA31/I15/SERCOM1.3/SWDIO), X3.2 (SWDIO)
TFT_BACKLITE: U$2.60 (PB31/I15/SERCOM5.0); also elsewhere on the board
TFT_CS: U$2.9 (PB06/I6/AIN8); also elsewhere on the board
TFT_RD: U$2.5 (PB04/I4/AIN6); also elsewhere on the board
TFT_RESET: U$2.1 (PA00/EINT0/SERCOM1.0); also elsewhere on the board
TFT_RS: U$2.6 (PB05/I5/AIN7); also elsewhere on the board
TFT_TE: U$2.10 (PB07/I7/AIN9); also elsewhere on the board
TFT_WR: U$2.12 (PB09/I9/AIN3/SERCOM4.1); also elsewhere on the board
TOUCH_XL: U$2.62 (PB01/I1/AIN13/SERCOM5.3); also elsewhere on the board
TOUCH_XR: U$2.11 (PB08/I8/AIN2/SERCOM4.0); also elsewhere on the board
TOUCH_YD: U$2.61 (PB00/I0/AIN12/SERCOM5.2); also elsewhere on the board
TOUCH_YU: U$2.15 (PA06/I6/VREFC/AIN6/SERCOM0.2); also elsewhere on the board
TXD: U$2.25 (PB12/I12/SERCOM4.0/I2SCK1); also elsewhere on the board
VBUS: PTC1.2, X4.VBUS
VDDCORE: C6.1, C9.1, C10.2, U$2.53 (VDDCORE)

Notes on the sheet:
ATSAMD51J20
8 TFT Data Pins ✓ 1 TFT Reset 4 TFT CS, RD, WR, C/D 1 TFT Backlight 4 resistive touch ✓ 1 light sensor ✓ 2 I2C Stemma ✓ 1 Analog Out 1 NeoPixel 1 D13 LED ✓ 2 USB ✓ 2 SWDIO ✓ 6 QSPI ✓ ------------ 41 total
STEMMA JST Conn.
Resistive Touch Any ADCs
SERCOM2 - SPI SERCOM4 - UART SERCOM5 - I2C
